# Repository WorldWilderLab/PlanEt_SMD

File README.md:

# PlanEt_SMD
smd version of planEt

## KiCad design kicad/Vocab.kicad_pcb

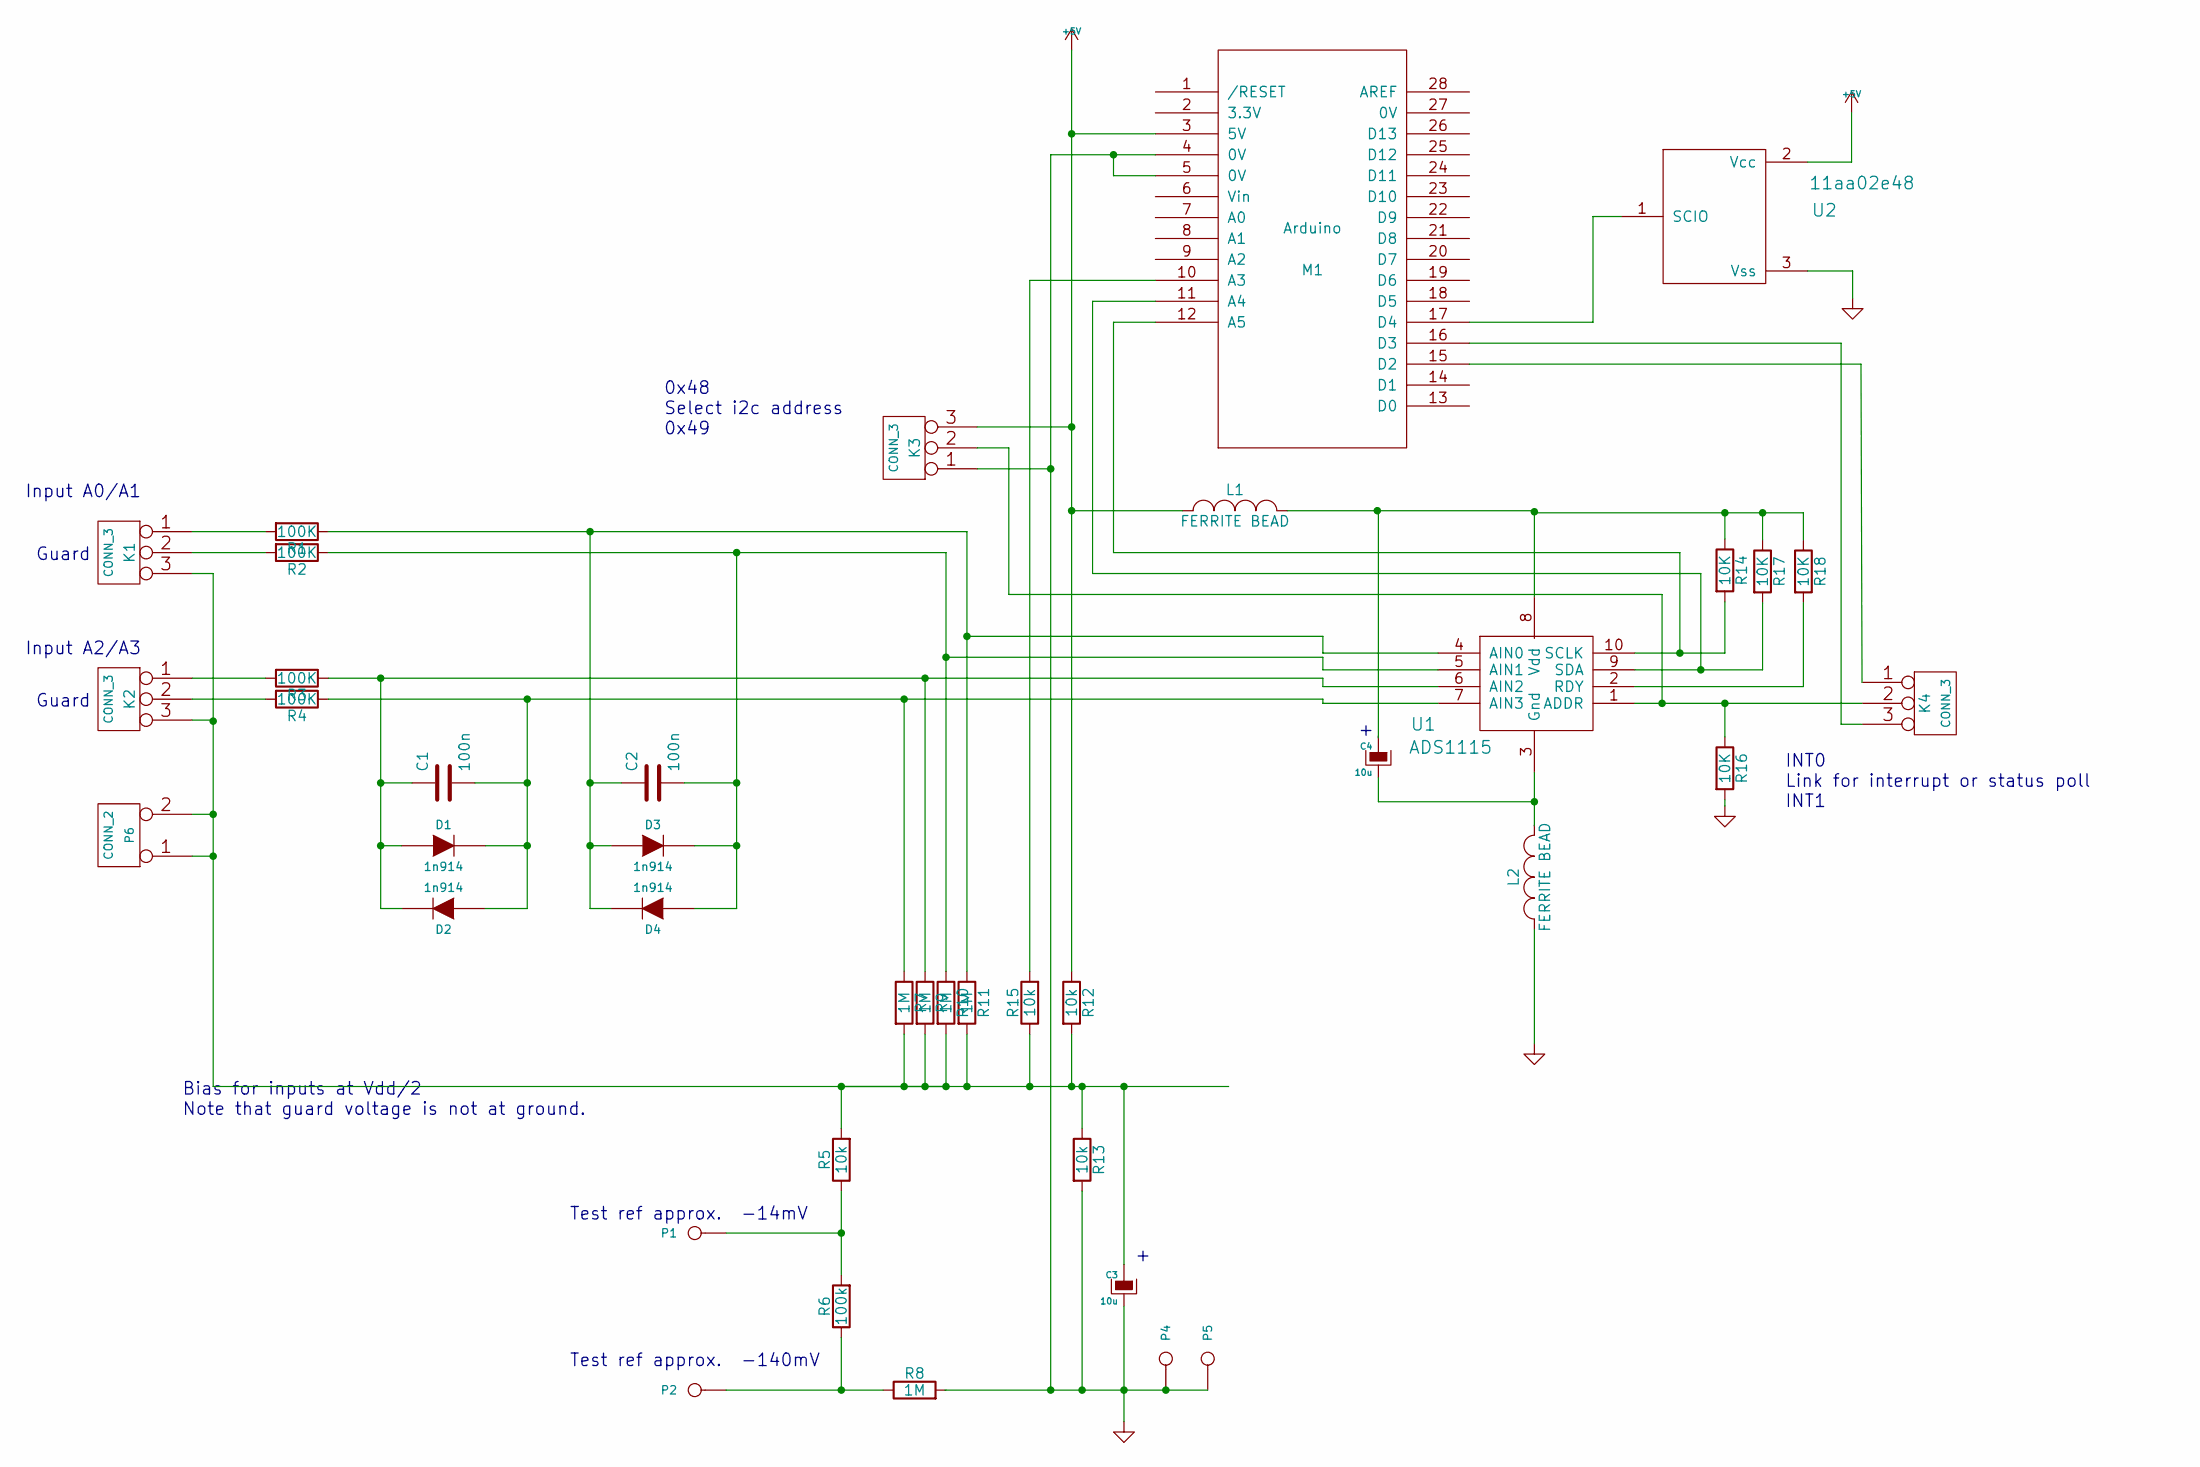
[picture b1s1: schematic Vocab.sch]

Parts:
C1, C2: 100n; C_1210
C3, C4: 10u; c_elec_5x5.8
D1, D2, D3, D4: 1n914; SOD-123
K1, K2, K3, K4: CONN_3; Socket_Strip_Straight_1x03
L1, L2: FERRITE BEAD; Choke_SMD_1206_Standard
M1: Arduino
P1, P2, P4, P5: CONN_1; Socket_Strip_Straight_1x01
P6: CONN_2; Socket_Strip_Straight_2x01
R1, R2, R3, R4: 100K; R_0805
R5, R12, R13, R15: 10k; R_0805
R6: 100k; R_0805
R7, R8, R9, R10, R11: 1M; R_0805
R14, R16, R17, R18: 10K; R_0805
U1: ADS1115; MSOP-10_3x3mm_Pitch0.5mm
U2: 11aa02e48; SOT-23

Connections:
+5V: K3.3, L1.1, M1.3 (5V), U2.2 (Vcc)
GND: C3.2, K3.1, L2.1, M1.4 (0V), M1.5 (0V), P4.1, P5.1, R13.2, R16.2, U2.3 (Vss)
unnamed: C1.1, D1.1 (A), D2.2 (K), R3.1, R9.1, U1.6 (AIN2)
unnamed: C1.2, D1.2 (K), D2.1 (A), R4.1, R7.1, U1.7 (AIN3)
unnamed: C2.1, D3.1 (A), D4.2 (K), R1.1, R11.1, U1.4 (AIN0)
unnamed: C2.2, D3.2 (K), D4.1 (A), R2.1, R10.1, U1.5 (AIN1)
unnamed: C3.1, K1.3, K2.3, P6.1, P6.2 (PM), R5.2, R7.2, R9.2, R10.2, R11.2, R12.2, R13.1, R15.1
unnamed: C4.2, U1.3 (Gnd)
unnamed: K1.1, R1.2
unnamed: K1.2 (PM), R2.2
unnamed: K2.1, R3.2
unnamed: K2.2 (PM), R4.2
unnamed: K3.2 (PM), K4.2 (PM), R16.1, U1.1 (ADDR)
unnamed: K4.1, M1.15 (D2)
unnamed: K4.3, M1.16 (D3)
unnamed: L1.2, R14.1, R17.1, R18.1, U1.8 (Vdd)
unnamed: M1.10 (A3), R15.2
unnamed: M1.11 (A4), R17.2, U1.9 (SDA)
unnamed: M1.12 (A5), R14.2, U1.10 (SCLK)
unnamed: M1.17 (D4), U2.1 (SCIO)
unnamed: P1.1, R5.1, R6.2
unnamed: P2.1, R6.1, R8.1
unnamed: R18.2, U1.2 (RDY)

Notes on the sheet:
Test ref approx. -140mV
Guard
Bias for inputs at Vdd/2 Note that guard voltage is not at ground.
Input A0/A1
Input A2/A3
Test ref approx. -14mV
INT0 Link for interrupt or status poll INT1
0x48 Select i2c address 0x49

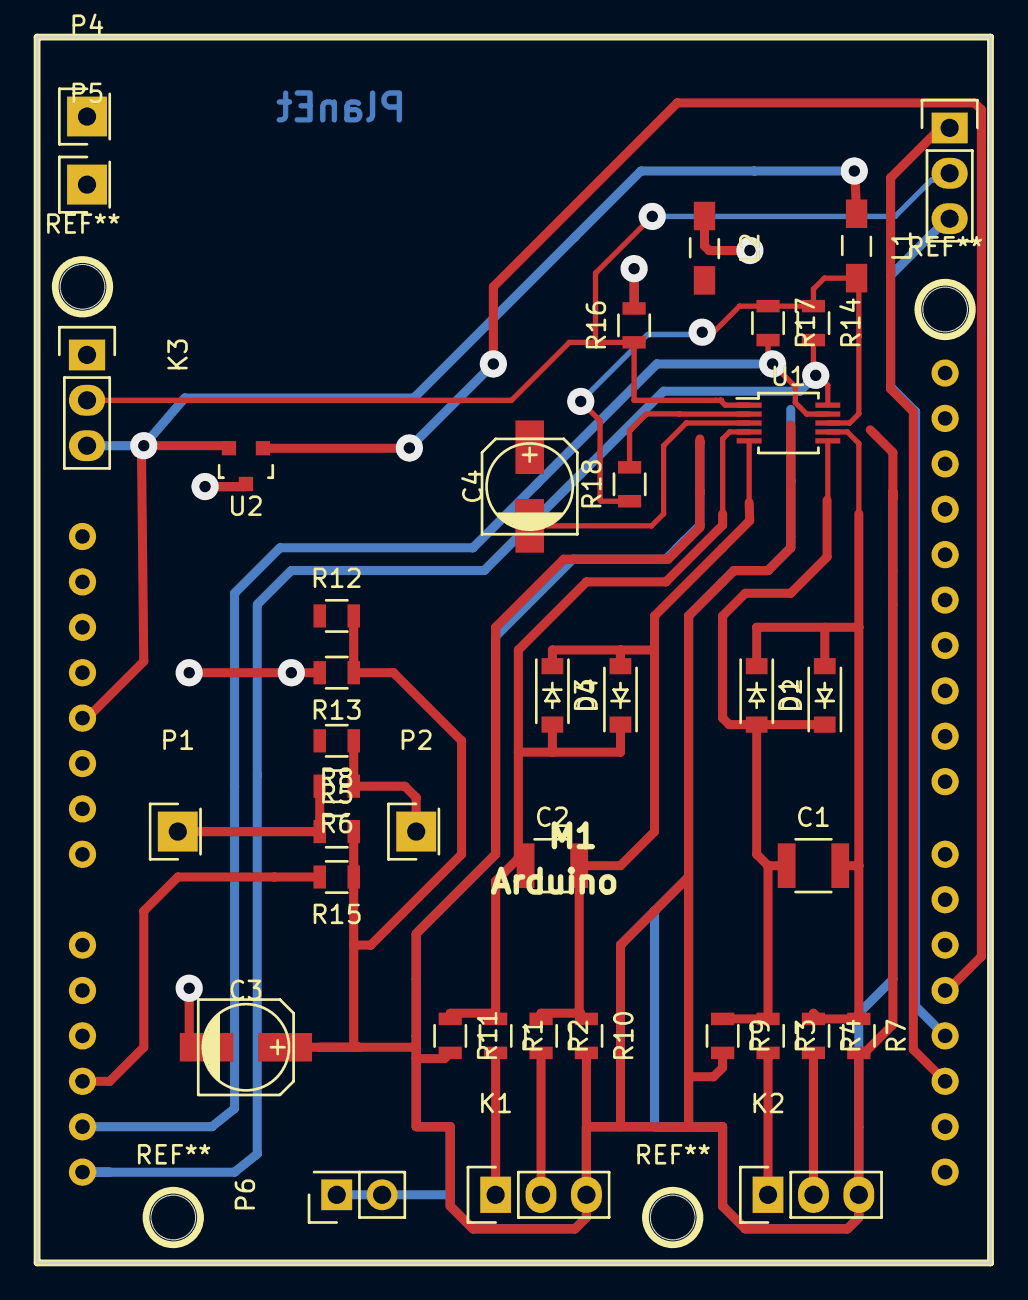
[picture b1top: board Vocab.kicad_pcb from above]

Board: 2 copper layers, 53.3 x 68.6 mm, 40 parts (0 on the bottom side), 23 nets.

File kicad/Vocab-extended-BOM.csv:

Id,Designator,Package,Quantity,Designation,Supplier and ref
1,"C1,C2",C2,2,100n, low voltage polypropylene 
2,"C3,C4",C2,2,10u,10V electrolytic or tantalum
3,"P1,P2",SIL-1,2,CONN_1,test point – single pin
4,"K1,K2,K4,K3",SIL-3,4,CONN_3,3 pin 0.1” rightangle header
5,"D2,D1,D4,D3",D3,4,1n914,silicon diode
6,P3,SIL-10,1,ads1115 breakout,adafruit ads1115
,,10 pin short header,,,
7,"P4,P5",1pin,2,CONN_1,wire loop for gnd test point
8,"R15,R12,R5,R13",R4-LARGE_PADS,4,10k,carbon film 1/8W 5%
9,R6,R4-LARGE_PADS,1,100k,carbon film 1/8W 5%
10,"R11,R7,R8,R9,R10",R4-LARGE_PADS,5,1M,carbon film 1/8W 5%
11,"R1,R4,R2,R3",R4-LARGE_PADS,4,100K,carbon film 1/8W 5%
12,R14,R4-LARGE_PADS,1,0R,wire link
13,M1,Arduino,1,Arduino,Uno
,,6 pin stacking header,1,,
,,8 pin stacking header,2,,
,,10 pin stacking header,1,,
,pcb,,,,

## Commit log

2015-09-15 added arduino files
2015-10-06 Added manufacturer part numbers (except for Rs - generic 0805) Added stacking connectors to bom manually
